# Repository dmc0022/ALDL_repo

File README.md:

# ALDL FPGA Modules

This repository contains FPGA-based hardware modules developed for the
Advanced Logic Design Lab (ALDL) project.

## Modules
- Accel-Demo: Accelerometer modules and demo
- CAP1188: Capacitive touch sensor demos
- HUB75: RGB LED matrix driver and animations
- LCD_Display: ILI9341 LCD + Breakout game renderer + keypad touch event handler/renderer 
- Schematics: Hardware schematics and PCB files
- Sensor Board: Comprehensive top file for both the LCD and CAP1188 board. Includes interfacing with the breakout connectors with a TMP117 temperature sensor via I2C.
- 3D-Models: Models of standoffs for LCD display as well as other STL files and UAH logo

Each module is self-contained and includes its own Quartus project files.

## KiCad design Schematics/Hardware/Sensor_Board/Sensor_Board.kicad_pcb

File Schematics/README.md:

# ALDL_Repo
collection of schematics, VHDL, CAD files for CPE 495 Project

3D Render of Sensor Board:

3D Render of LED Driver Board:

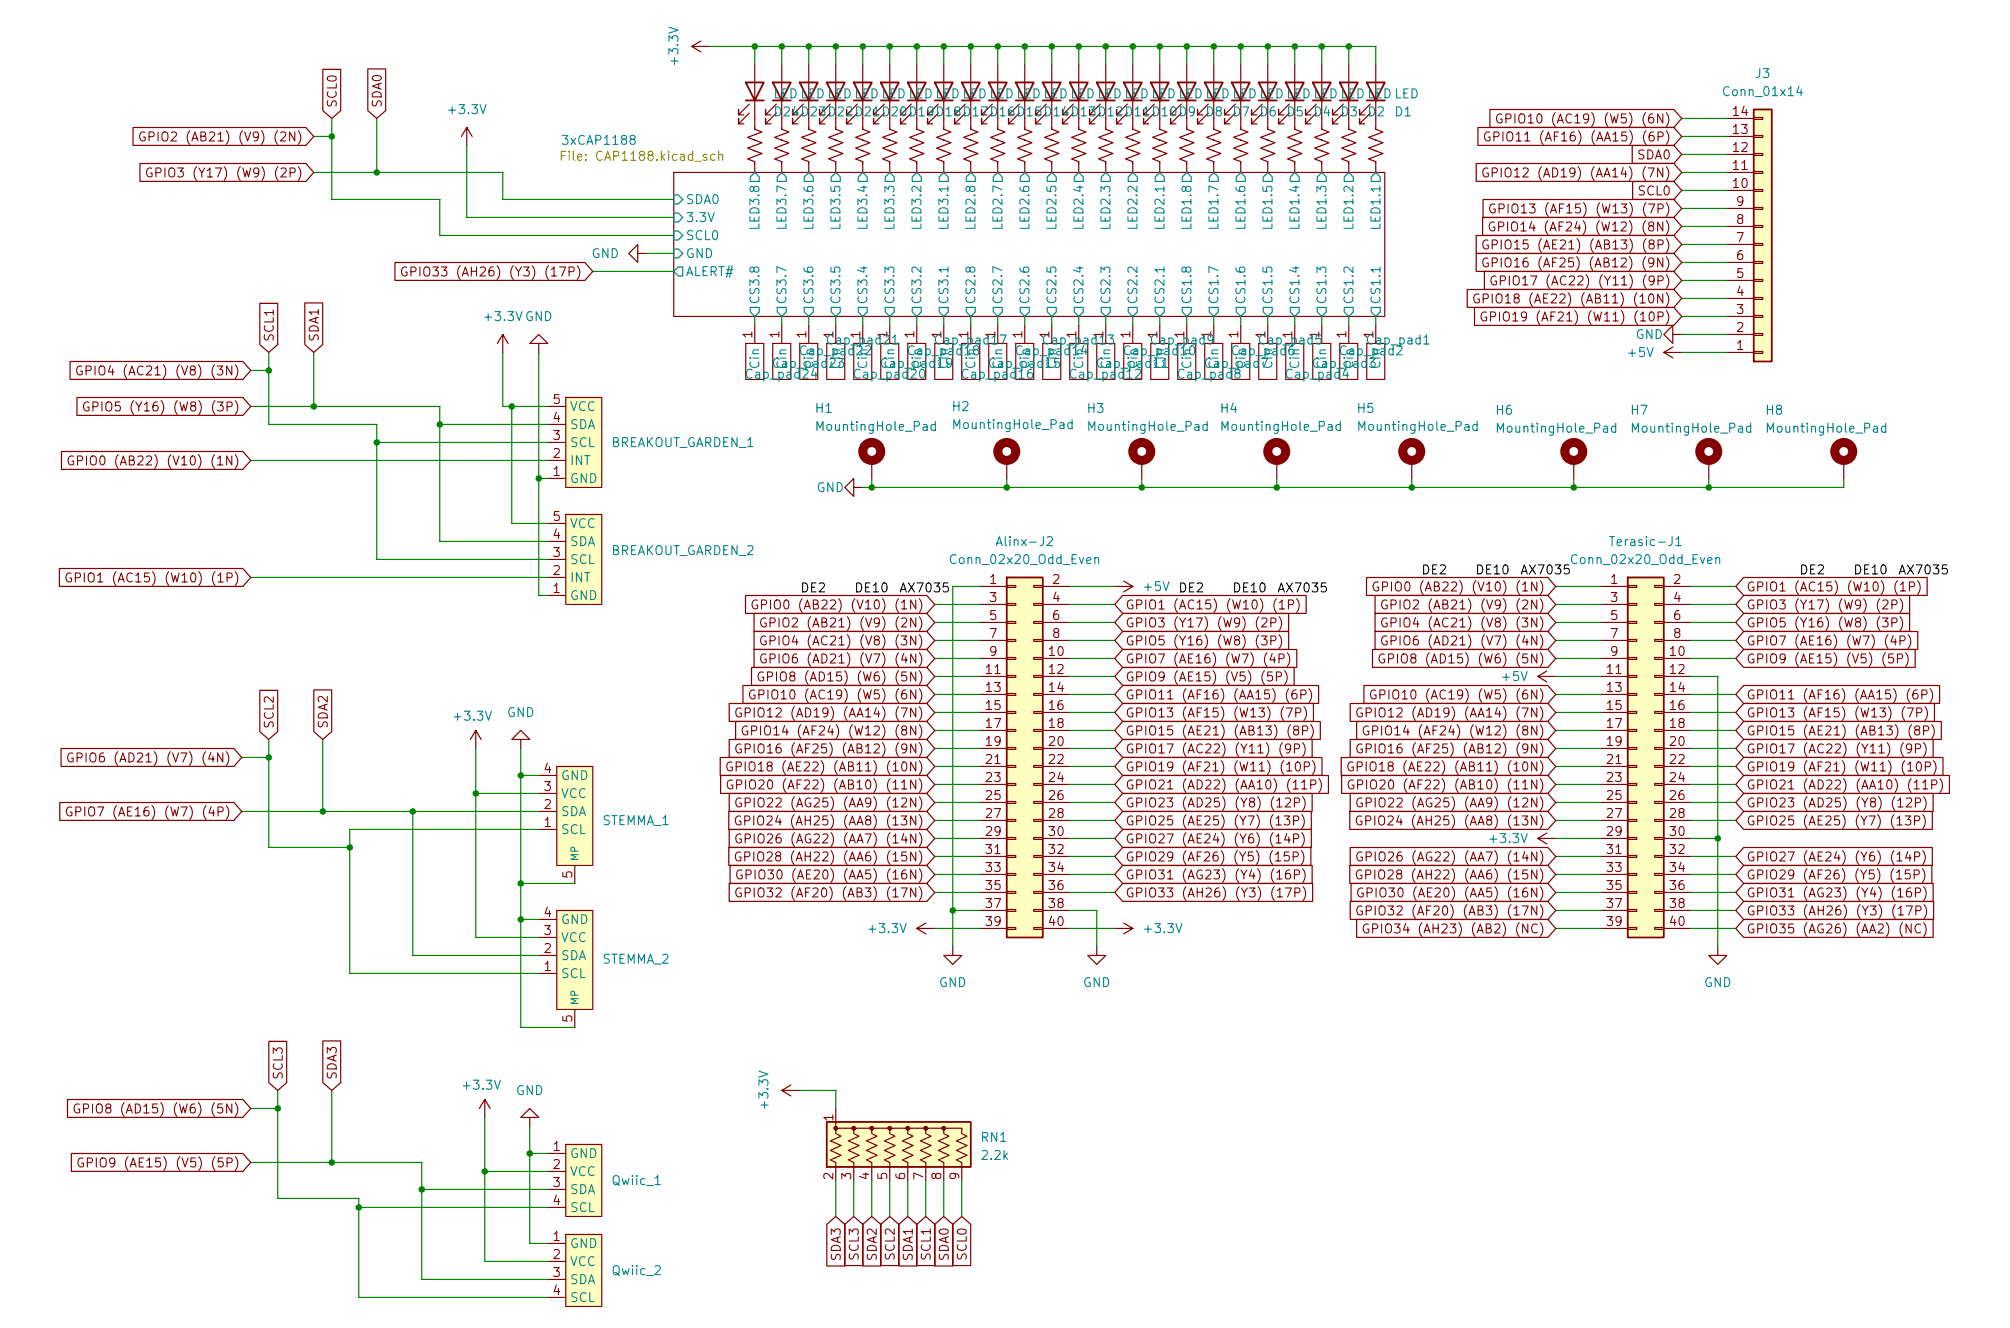
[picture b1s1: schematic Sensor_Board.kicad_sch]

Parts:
Alinx-J2: Conn_02x20_Odd_Even; IDC-Header_2x20_P2.54mm_Vertical
BREAKOUT_GARDEN_1, BREAKOUT_GARDEN_2: PinHeader_1x05_P2.54mm_Vertical
Cap_pad1, Cap_pad2, Cap_pad3, Cap_pad4, Cap_pad5, Cap_pad6, Cap_pad7, Cap_pad8, Cap_pad9, Cap_pad10, Cap_pad11, Cap_pad12, Cap_pad13, Cap_pad14, Cap_pad15, Cap_pad16, Cap_pad17, Cap_pad18, Cap_pad19, Cap_pad20, Cap_pad21, Cap_pad22, Cap_pad23, Cap_pad24: Cap_pad
D1, D2, D3, D4, D5, D6, D7, D8, D9, D10, D11, D12, D13, D14, D15, D16, D17, D18, D19, D20, D21, D22, D23, D24: LED; D_0805_2012Metric
H1, H2, H3, H4, H5, H6, H7, H8: MountingHole_Pad; MountingHole_2.5mm_Pad_Via
J3: Conn_01x14; PinSocket_1x14_P2.54mm_Vertical
Qwiic_1, Qwiic_2: JST_SH_SM04B-SRSS-TB_1x04-1MP_P1.00mm_Horizontal
R7, R8, R9, R10, R11, R12, R13, R14, R15, R16, R17, R18, R19, R20, R21, R22, R23, R24, R25, R26, R27, R28, R29, R30: 2.2k; R_0805_2012Metric
RN1: 2.2k; R_Array_SIP9
STEMMA_1, STEMMA_2: JST_PH_S4B-PH-SM4-TB_1x04-1MP_P2.00mm_Horizontal
Terasic-J1: Conn_02x20_Odd_Even; IDC-Header_2x20_P2.54mm_Vertical

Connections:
+3.3V: Alinx-J2.39, Alinx-J2.40, BREAKOUT_GARDEN_1.5 (VCC), BREAKOUT_GARDEN_2.5 (VCC), D1.2 (A), D2.2 (A), D3.2 (A), D4.2 (A), D5.2 (A), D6.2 (A), D7.2 (A), D8.2 (A), D9.2 (A), D10.2 (A), D11.2 (A), D12.2 (A), D13.2 (A), D14.2 (A), D15.2 (A), D16.2 (A), D17.2 (A), D18.2 (A), D19.2 (A), D20.2 (A), D21.2 (A), D22.2 (A), D23.2 (A), D24.2 (A), Qwiic_1.2 (VCC), Qwiic_2.2 (VCC), RN1.1 (common), STEMMA_1.3 (VCC), STEMMA_2.3 (VCC), Terasic-J1.29; also elsewhere on the board
+5V: Alinx-J2.2, J3.1, Terasic-J1.11
/3xCAP1188/CS1.1: Cap_pad1.1 (Cin); also elsewhere on the board
/3xCAP1188/CS1.2: Cap_pad2.1 (Cin); also elsewhere on the board
/3xCAP1188/CS1.3: Cap_pad3.1 (Cin); also elsewhere on the board
/3xCAP1188/CS1.4: Cap_pad4.1 (Cin); also elsewhere on the board
/3xCAP1188/CS1.5: Cap_pad5.1 (Cin); also elsewhere on the board
/3xCAP1188/CS1.6: Cap_pad6.1 (Cin); also elsewhere on the board
/3xCAP1188/CS1.7: Cap_pad7.1 (Cin); also elsewhere on the board
/3xCAP1188/CS1.8: Cap_pad8.1 (Cin); also elsewhere on the board
/3xCAP1188/CS2.1: Cap_pad9.1 (Cin); also elsewhere on the board
/3xCAP1188/CS2.2: Cap_pad10.1 (Cin); also elsewhere on the board
/3xCAP1188/CS2.3: Cap_pad11.1 (Cin); also elsewhere on the board
/3xCAP1188/CS2.4: Cap_pad12.1 (Cin); also elsewhere on the board
/3xCAP1188/CS2.5: Cap_pad13.1 (Cin); also elsewhere on the board
/3xCAP1188/CS2.6: Cap_pad14.1 (Cin); also elsewhere on the board
/3xCAP1188/CS2.7: Cap_pad15.1 (Cin); also elsewhere on the board
/3xCAP1188/CS2.8: Cap_pad16.1 (Cin); also elsewhere on the board
/3xCAP1188/CS3.1: Cap_pad17.1 (Cin); also elsewhere on the board
/3xCAP1188/CS3.2: Cap_pad18.1 (Cin); also elsewhere on the board
/3xCAP1188/CS3.3: Cap_pad19.1 (Cin); also elsewhere on the board
/3xCAP1188/CS3.4: Cap_pad20.1 (Cin); also elsewhere on the board
/3xCAP1188/CS3.5: Cap_pad21.1 (Cin); also elsewhere on the board
/3xCAP1188/CS3.6: Cap_pad22.1 (Cin); also elsewhere on the board
/3xCAP1188/CS3.7: Cap_pad23.1 (Cin); also elsewhere on the board
/3xCAP1188/CS3.8: Cap_pad24.1 (Cin); also elsewhere on the board
/3xCAP1188/LED1.1: R29.2; also elsewhere on the board
/3xCAP1188/LED1.2: R28.2; also elsewhere on the board
/3xCAP1188/LED1.3: R27.2; also elsewhere on the board
/3xCAP1188/LED1.4: R26.2; also elsewhere on the board
/3xCAP1188/LED1.5: R25.2; also elsewhere on the board
/3xCAP1188/LED1.6: R24.2; also elsewhere on the board
/3xCAP1188/LED1.7: R23.2; also elsewhere on the board
/3xCAP1188/LED1.8: R22.2; also elsewhere on the board
/3xCAP1188/LED2.1: R21.2; also elsewhere on the board
/3xCAP1188/LED2.2: R20.2; also elsewhere on the board
/3xCAP1188/LED2.3: R19.2; also elsewhere on the board
/3xCAP1188/LED2.4: R18.2; also elsewhere on the board
/3xCAP1188/LED2.5: R17.2; also elsewhere on the board
/3xCAP1188/LED2.6: R16.2; also elsewhere on the board
/3xCAP1188/LED2.7: R15.2; also elsewhere on the board
/3xCAP1188/LED2.8: R14.2; also elsewhere on the board
/3xCAP1188/LED3.1: R13.2; also elsewhere on the board
/3xCAP1188/LED3.2: R12.2; also elsewhere on the board
/3xCAP1188/LED3.3: R11.2; also elsewhere on the board
/3xCAP1188/LED3.4: R10.2; also elsewhere on the board
/3xCAP1188/LED3.5: R9.2; also elsewhere on the board
/3xCAP1188/LED3.6: R8.2; also elsewhere on the board
/3xCAP1188/LED3.7: R7.2; also elsewhere on the board
/3xCAP1188/LED3.8: R30.2; also elsewhere on the board
GND: Alinx-J2.1, Alinx-J2.37, Alinx-J2.38, BREAKOUT_GARDEN_1.1 (GND), BREAKOUT_GARDEN_2.1 (GND), H1.1, H2.1, H3.1, H4.1, H5.1, H6.1, H7.1, H8.1, J3.2, Qwiic_1.1 (GND), Qwiic_2.1 (GND), STEMMA_1.4 (GND), STEMMA_1.5 (MP), STEMMA_2.4 (GND), STEMMA_2.5 (MP), Terasic-J1.12, Terasic-J1.30; also elsewhere on the board
GPIO0 (AB22) (V10) (1N): Alinx-J2.3, BREAKOUT_GARDEN_1.2 (INT), Terasic-J1.1
GPIO1 (AC15) (W10) (1P): Alinx-J2.4, BREAKOUT_GARDEN_2.2 (INT), Terasic-J1.2
GPIO2 (AB21) (V9) (2N): Alinx-J2.5, J3.10, RN1.9 (R8), Terasic-J1.3; also elsewhere on the board
GPIO3 (Y17) (W9) (2P): Alinx-J2.6, J3.12, RN1.8 (R7), Terasic-J1.4; also elsewhere on the board
GPIO4 (AC21) (V8) (3N): Alinx-J2.7, BREAKOUT_GARDEN_1.3 (SCL), BREAKOUT_GARDEN_2.3 (SCL), RN1.7 (R6), Terasic-J1.5
GPIO5 (Y16) (W8) (3P): Alinx-J2.8, BREAKOUT_GARDEN_1.4 (SDA), BREAKOUT_GARDEN_2.4 (SDA), RN1.6 (R5), Terasic-J1.6
GPIO6 (AD21) (V7) (4N): Alinx-J2.9, RN1.5 (R4), STEMMA_1.1 (SCL), STEMMA_2.1 (SCL), Terasic-J1.7
GPIO7 (AE16) (W7) (4P): Alinx-J2.10, RN1.4 (R3), STEMMA_1.2 (SDA), STEMMA_2.2 (SDA), Terasic-J1.8
GPIO8 (AD15) (W6) (5N): Alinx-J2.11, Qwiic_1.4 (SCL), Qwiic_2.4 (SCL), RN1.3 (R2), Terasic-J1.9
GPIO9 (AE15) (V5) (5P): Alinx-J2.12, Qwiic_1.3 (SDA), Qwiic_2.3 (SDA), RN1.2 (R1), Terasic-J1.10
GPIO10 (AC19) (W5) (6N): Alinx-J2.13, J3.14, Terasic-J1.13
GPIO11 (AF16) (AA15) (6P): Alinx-J2.14, J3.13, Terasic-J1.14
GPIO12 (AD19) (AA14) (7N): Alinx-J2.15, J3.11, Terasic-J1.15
GPIO13 (AF15) (W13) (7P): Alinx-J2.16, J3.9, Terasic-J1.16
GPIO14 (AF24) (W12) (8N): Alinx-J2.17, J3.8, Terasic-J1.17
GPIO15 (AE21) (AB13) (8P): Alinx-J2.18, J3.7, Terasic-J1.18
GPIO16 (AF25) (AB12) (9N): Alinx-J2.19, J3.6, Terasic-J1.19
GPIO17 (AC22) (Y11) (9P): Alinx-J2.20, J3.5, Terasic-J1.20
GPIO18 (AE22) (AB11) (10N): Alinx-J2.21, J3.4, Terasic-J1.21
GPIO19 (AF21) (W11) (10P): Alinx-J2.22, J3.3, Terasic-J1.22
GPIO20 (AF22) (AB10) (11N): Alinx-J2.23, Terasic-J1.23
GPIO21 (AD22) (AA10) (11P): Alinx-J2.24, Terasic-J1.24
GPIO22 (AG25) (AA9) (12N): Alinx-J2.25, Terasic-J1.25
GPIO23 (AD25) (Y8) (12P): Alinx-J2.26, Terasic-J1.26
GPIO24 (AH25) (AA8) (13N): Alinx-J2.27, Terasic-J1.27
GPIO25 (AE25) (Y7) (13P): Alinx-J2.28, Terasic-J1.28
GPIO26 (AG22) (AA7) (14N): Alinx-J2.29, Terasic-J1.31
GPIO27 (AE24) (Y6) (14P): Alinx-J2.30, Terasic-J1.32
GPIO28 (AH22) (AA6) (15N): Alinx-J2.31, Terasic-J1.33
GPIO29 (AF26) (Y5) (15P): Alinx-J2.32, Terasic-J1.34
GPIO30 (AE20) (AA5) (16N): Alinx-J2.33, Terasic-J1.35
GPIO31 (AG23) (Y4) (16P): Alinx-J2.34, Terasic-J1.36
GPIO32 (AF20) (AB3) (17N): Alinx-J2.35, Terasic-J1.37
GPIO33 (AH26) (Y3) (17P): Alinx-J2.36, Terasic-J1.38; also elsewhere on the board
GPIO34 (AH23) (AB2) (NC): Terasic-J1.39
GPIO35 (AG26) (AA2) (NC): Terasic-J1.40
unnamed: D1.1 (K), R29.1
unnamed: D2.1 (K), R28.1
unnamed: D3.1 (K), R27.1
unnamed: D4.1 (K), R26.1
unnamed: D5.1 (K), R25.1
unnamed: D6.1 (K), R24.1
unnamed: D7.1 (K), R23.1
unnamed: D8.1 (K), R22.1
unnamed: D9.1 (K), R21.1
unnamed: D10.1 (K), R20.1
unnamed: D11.1 (K), R19.1
unnamed: D12.1 (K), R18.1
unnamed: D13.1 (K), R17.1
unnamed: D14.1 (K), R16.1
unnamed: D15.1 (K), R15.1
unnamed: D16.1 (K), R14.1
unnamed: D17.1 (K), R13.1
unnamed: D18.1 (K), R12.1
unnamed: D19.1 (K), R11.1
unnamed: D20.1 (K), R10.1
unnamed: D21.1 (K), R9.1
unnamed: D22.1 (K), R8.1
unnamed: D23.1 (K), R7.1
unnamed: D24.1 (K), R30.1

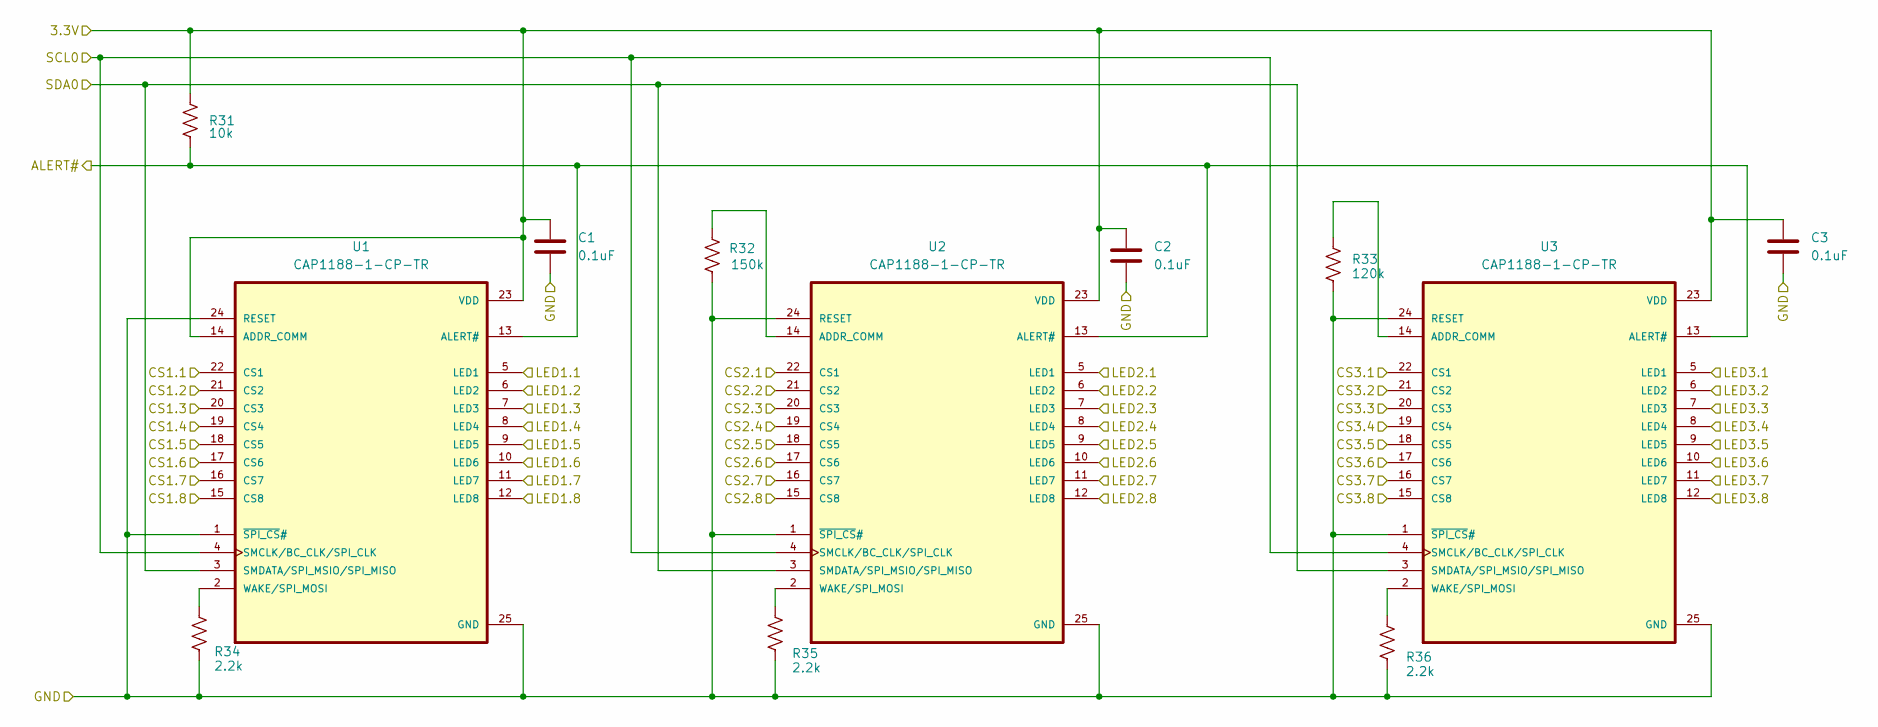
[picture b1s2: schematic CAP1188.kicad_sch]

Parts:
C1, C2, C3: 0.1uF; C_0805_2012Metric
R31: 10k; R_Axial_DIN0207_L6.3mm_D2.5mm_P10.16mm_Horizontal
R32: 150k; R_Axial_DIN0207_L6.3mm_D2.5mm_P10.16mm_Horizontal
R33: 120k; R_Axial_DIN0207_L6.3mm_D2.5mm_P10.16mm_Horizontal
R34, R35, R36: 2.2k; R_Axial_DIN0207_L6.3mm_D2.5mm_P10.16mm_Horizontal
U1, U2, U3: CAP1188-1-CP-TR; QFN-24-1EP_4x4mm_P0.5mm_EP2.7x2.6mm; PARTREV 02-09-15

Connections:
+3.3V: C1.1, C2.1, C3.1, R31.1, U1.14 (ADDR_COMM), U1.23 (VDD), U2.23 (VDD), U3.23 (VDD); also elsewhere on the board
/3xCAP1188/CS1.1: U1.22 (CS1); also elsewhere on the board
/3xCAP1188/CS1.2: U1.21 (CS2); also elsewhere on the board
/3xCAP1188/CS1.3: U1.20 (CS3); also elsewhere on the board
/3xCAP1188/CS1.4: U1.19 (CS4); also elsewhere on the board
/3xCAP1188/CS1.5: U1.18 (CS5); also elsewhere on the board
/3xCAP1188/CS1.6: U1.17 (CS6); also elsewhere on the board
/3xCAP1188/CS1.7: U1.16 (CS7); also elsewhere on the board
/3xCAP1188/CS1.8: U1.15 (CS8); also elsewhere on the board
/3xCAP1188/CS2.1: U2.22 (CS1); also elsewhere on the board
/3xCAP1188/CS2.2: U2.21 (CS2); also elsewhere on the board
/3xCAP1188/CS2.3: U2.20 (CS3); also elsewhere on the board
/3xCAP1188/CS2.4: U2.19 (CS4); also elsewhere on the board
/3xCAP1188/CS2.5: U2.18 (CS5); also elsewhere on the board
/3xCAP1188/CS2.6: U2.17 (CS6); also elsewhere on the board
/3xCAP1188/CS2.7: U2.16 (CS7); also elsewhere on the board
/3xCAP1188/CS2.8: U2.15 (CS8); also elsewhere on the board
/3xCAP1188/CS3.1: U3.22 (CS1); also elsewhere on the board
/3xCAP1188/CS3.2: U3.21 (CS2); also elsewhere on the board
/3xCAP1188/CS3.3: U3.20 (CS3); also elsewhere on the board
/3xCAP1188/CS3.4: U3.19 (CS4); also elsewhere on the board
/3xCAP1188/CS3.5: U3.18 (CS5); also elsewhere on the board
/3xCAP1188/CS3.6: U3.17 (CS6); also elsewhere on the board
/3xCAP1188/CS3.7: U3.16 (CS7); also elsewhere on the board
/3xCAP1188/CS3.8: U3.15 (CS8); also elsewhere on the board
/3xCAP1188/LED1.1: U1.5 (LED1); also elsewhere on the board
/3xCAP1188/LED1.2: U1.6 (LED2); also elsewhere on the board
/3xCAP1188/LED1.3: U1.7 (LED3); also elsewhere on the board
/3xCAP1188/LED1.4: U1.8 (LED4); also elsewhere on the board
/3xCAP1188/LED1.5: U1.9 (LED5); also elsewhere on the board
/3xCAP1188/LED1.6: U1.10 (LED6); also elsewhere on the board
/3xCAP1188/LED1.7: U1.11 (LED7); also elsewhere on the board
/3xCAP1188/LED1.8: U1.12 (LED8); also elsewhere on the board
/3xCAP1188/LED2.1: U2.5 (LED1); also elsewhere on the board
/3xCAP1188/LED2.2: U2.6 (LED2); also elsewhere on the board
/3xCAP1188/LED2.3: U2.7 (LED3); also elsewhere on the board
/3xCAP1188/LED2.4: U2.8 (LED4); also elsewhere on the board
/3xCAP1188/LED2.5: U2.9 (LED5); also elsewhere on the board
/3xCAP1188/LED2.6: U2.10 (LED6); also elsewhere on the board
/3xCAP1188/LED2.7: U2.11 (LED7); also elsewhere on the board
/3xCAP1188/LED2.8: U2.12 (LED8); also elsewhere on the board
/3xCAP1188/LED3.1: U3.5 (LED1); also elsewhere on the board
/3xCAP1188/LED3.2: U3.6 (LED2); also elsewhere on the board
/3xCAP1188/LED3.3: U3.7 (LED3); also elsewhere on the board
/3xCAP1188/LED3.4: U3.8 (LED4); also elsewhere on the board
/3xCAP1188/LED3.5: U3.9 (LED5); also elsewhere on the board
/3xCAP1188/LED3.6: U3.10 (LED6); also elsewhere on the board
/3xCAP1188/LED3.7: U3.11 (LED7); also elsewhere on the board
/3xCAP1188/LED3.8: U3.12 (LED8); also elsewhere on the board
GND: C1.2, C2.2, C3.2, R32.2, R33.2, R34.2, R35.2, R36.2, U1.1 (~SPI_CS#), U1.24 (RESET), U1.25 (GND), U2.1 (~SPI_CS#), U2.24 (RESET), U2.25 (GND), U3.1 (~SPI_CS#), U3.24 (RESET), U3.25 (GND); also elsewhere on the board
GPIO2 (AB21) (V9) (2N): U1.4 (SMCLK/BC_CLK/SPI_CLK), U2.4 (SMCLK/BC_CLK/SPI_CLK), U3.4 (SMCLK/BC_CLK/SPI_CLK); also elsewhere on the board
GPIO3 (Y17) (W9) (2P): U1.3 (SMDATA/SPI_MSIO/SPI_MISO), U2.3 (SMDATA/SPI_MSIO/SPI_MISO), U3.3 (SMDATA/SPI_MSIO/SPI_MISO); also elsewhere on the board
GPIO33 (AH26) (Y3) (17P): R31.2, U1.13 (ALERT#), U2.13 (ALERT#), U3.13 (ALERT#); also elsewhere on the board
unnamed: R34.1, U1.2 (WAKE/SPI_MOSI)
unnamed: R32.1, U2.14 (ADDR_COMM)
unnamed: R35.1, U2.2 (WAKE/SPI_MOSI)
unnamed: R33.1, U3.14 (ADDR_COMM)
unnamed: R36.1, U3.2 (WAKE/SPI_MOSI)

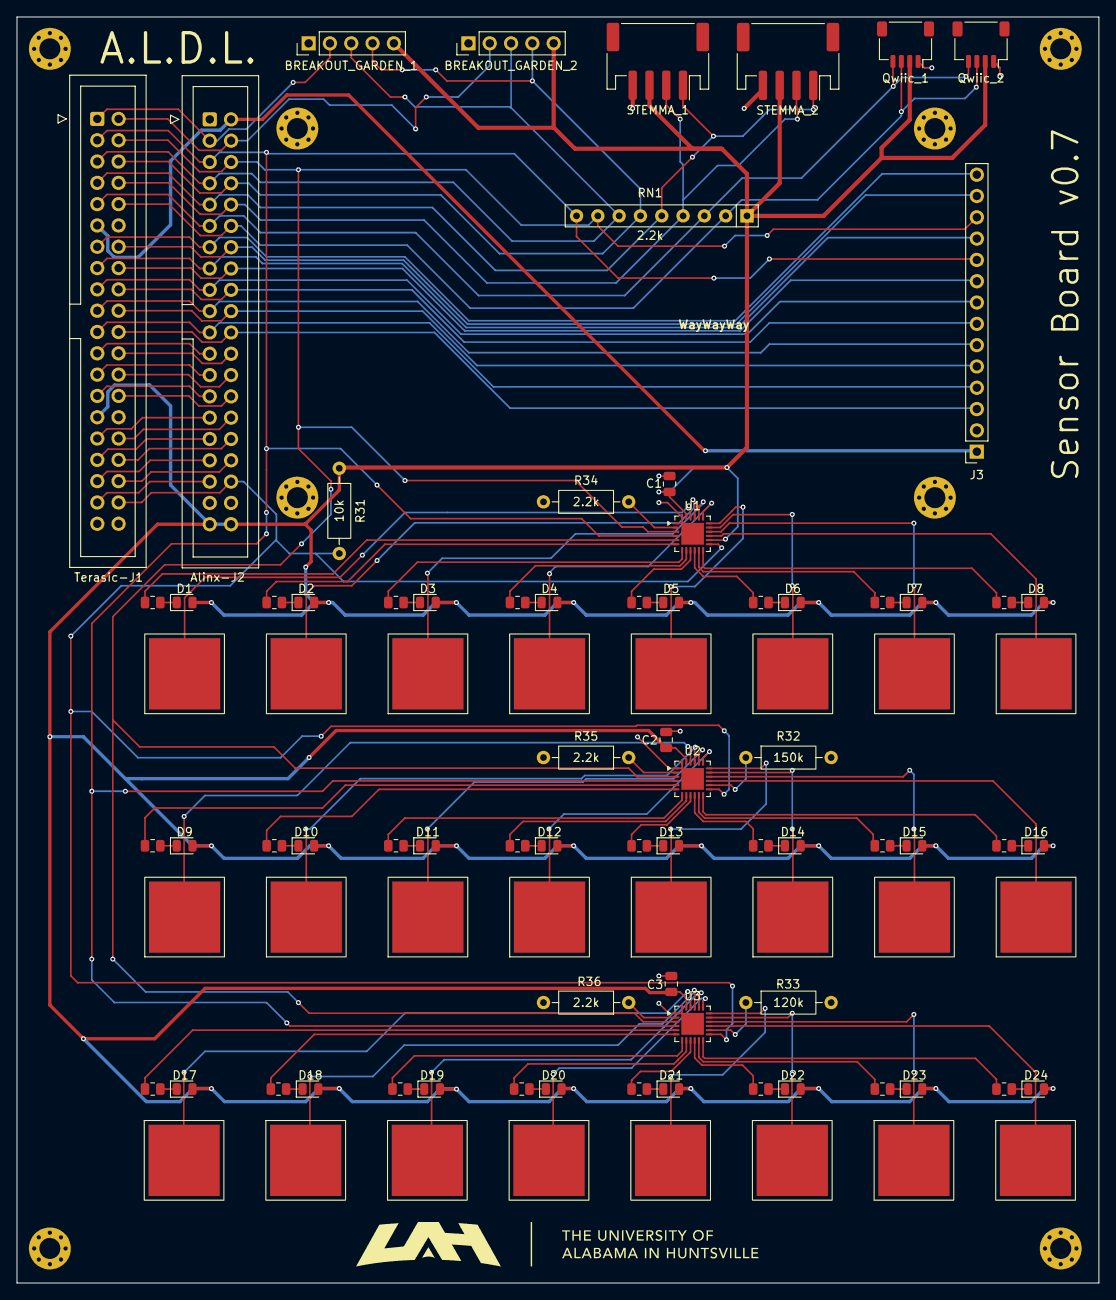
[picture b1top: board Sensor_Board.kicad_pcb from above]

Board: 2 copper layers, 129.0 x 150.9 mm, 102 parts (0 on the bottom side), 114 nets.

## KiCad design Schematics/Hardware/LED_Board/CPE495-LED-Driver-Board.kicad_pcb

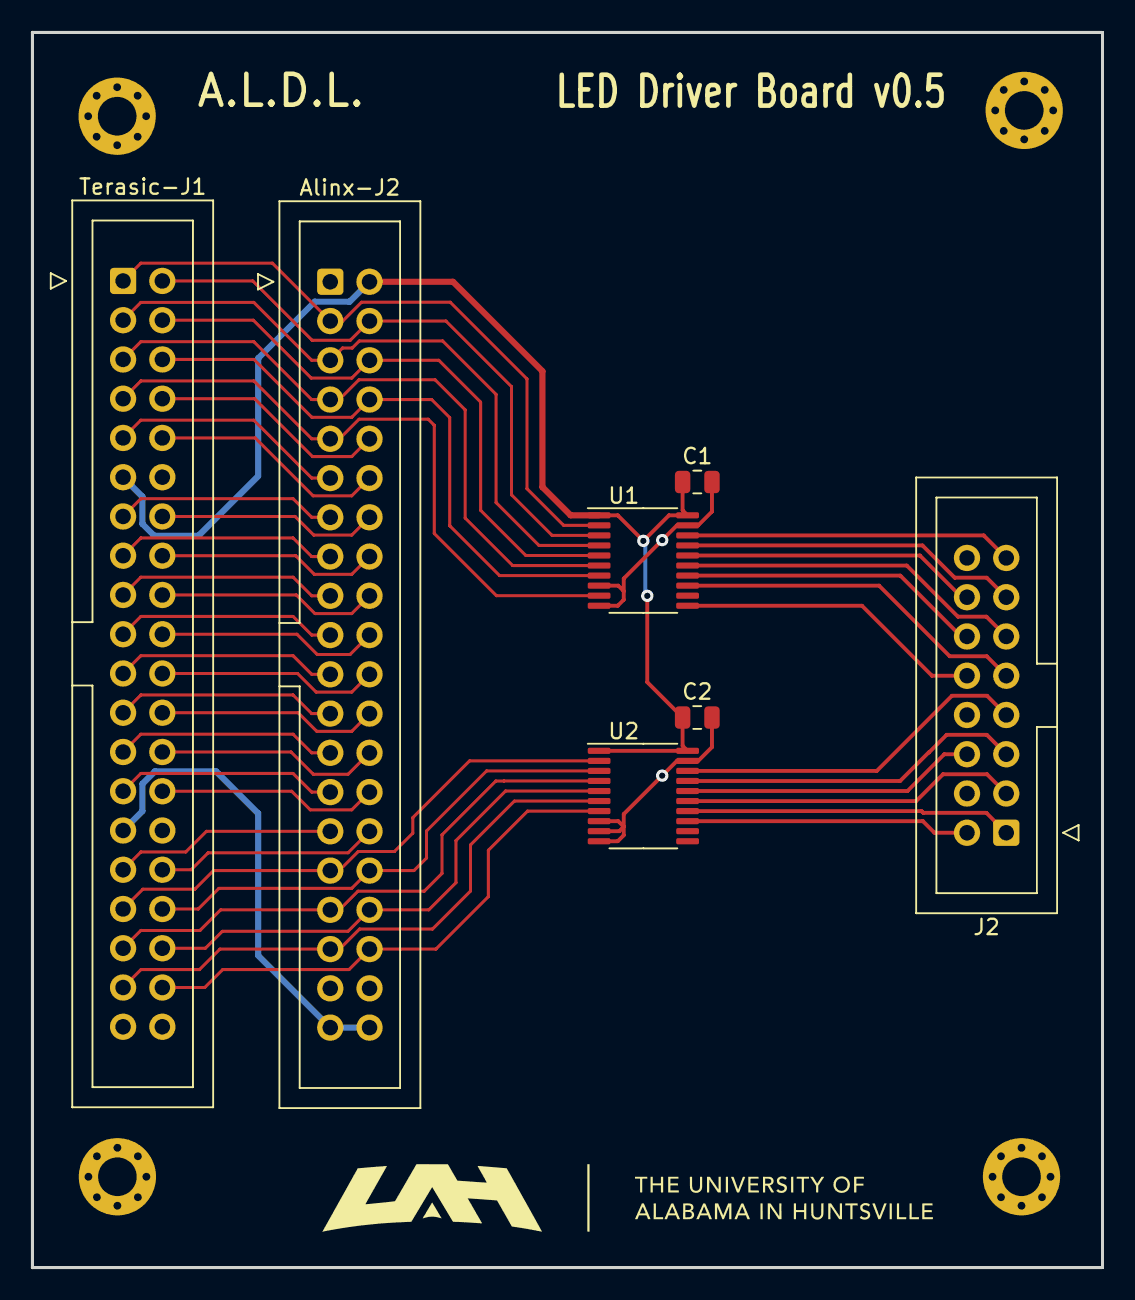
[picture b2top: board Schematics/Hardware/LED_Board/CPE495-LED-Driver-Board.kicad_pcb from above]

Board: 2 copper layers, 69.2 x 79.9 mm, 11 parts (0 on the bottom side), 50 nets.

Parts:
Alinx-J2: Conn_02x20_Odd_Even; IDC-Header_2x20_P2.54mm_Vertical
C1, C2: 0.1uF; C_0805_2012Metric
H1, H2, H3, H4: MountingHole_Pad; MountingHole_2.5mm_Pad_Via
J2: Conn_02x08_Odd_Even; IDC-Header_2x08_P2.54mm_Vertical
Terasic-J1: Conn_02x20_Odd_Even; IDC-Header_2x20_P2.54mm_Vertical
U1, U2: 74AHCT245; TSSOP-20_4.4x6.5mm_P0.65mm

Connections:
+3.3V: Alinx-J2.39, Alinx-J2.40, Terasic-J1.29
+5V: Alinx-J2.2, C1.1, C2.1, Terasic-J1.11, U1.1 (A->B), U1.20 (VCC), U2.1 (A->B), U2.20 (VCC)
A: J2.9, U1.13 (B5)
B: J2.10, U1.11 (B7)
B1: J2.3, U2.15 (B3)
B2: J2.7, U2.18 (B0)
C: J2.11, U1.15 (B3)
CLK: J2.13, U1.17 (B1)
D: J2.12, U1.14 (B4)
G1: J2.2, U2.13 (B5)
G2: J2.6, U2.16 (B2)
GND: Alinx-J2.1, Alinx-J2.37, Alinx-J2.38, C1.2, C2.2, H1.1, H2.1, H3.1, H4.1, J2.4, J2.8, J2.16, Terasic-J1.12, Terasic-J1.30, U1.8 (A6), U1.10 (GND), U1.19 (CE), U2.8 (A6), U2.9 (A7), U2.10 (GND), U2.19 (CE)
GPIO0 (AB22) (V10) (1N): Alinx-J2.3, Terasic-J1.1, U1.2 (A0)
GPIO1 (AC15) (W10) (1P): Alinx-J2.4, Terasic-J1.2, U1.3 (A1)
GPIO2 (AB21) (V9) (2N): Alinx-J2.5, Terasic-J1.3, U1.4 (A2)
GPIO3 (Y17) (W9) (2P): Alinx-J2.6, Terasic-J1.4, U1.5 (A3)
GPIO4 (AC21) (V8) (3N): Alinx-J2.7, Terasic-J1.5, U1.6 (A4)
GPIO5 (Y16) (W8) (3P): Alinx-J2.8, Terasic-J1.6, U1.7 (A5)
GPIO6 (AD21) (V7) (4N): Alinx-J2.9, Terasic-J1.7, U1.9 (A7)
GPIO7 (AE16) (W7) (4P): Alinx-J2.10, Terasic-J1.8
GPIO8 (AD15) (W6) (5N): Alinx-J2.11, Terasic-J1.9
GPIO9 (AE15) (V5) (5P): Alinx-J2.12, Terasic-J1.10
GPIO10 (AC19) (W5) (6N): Alinx-J2.13, Terasic-J1.13
GPIO11 (AF16) (AA15) (6P): Alinx-J2.14, Terasic-J1.14
GPIO12 (AD19) (AA14) (7N): Alinx-J2.15, Terasic-J1.15
GPIO13 (AF15) (W13) (7P): Alinx-J2.16, Terasic-J1.16
GPIO14 (AF24) (W12) (8N): Alinx-J2.17, Terasic-J1.17
GPIO15 (AE21) (AB13) (8P): Alinx-J2.18, Terasic-J1.18
GPIO16 (AF25) (AB12) (9N): Alinx-J2.19, Terasic-J1.19
GPIO17 (AC22) (Y11) (9P): Alinx-J2.20, Terasic-J1.20
GPIO18 (AE22) (AB11) (10N): Alinx-J2.21, Terasic-J1.21
GPIO19 (AF21) (W11) (10P): Alinx-J2.22, Terasic-J1.22
GPIO20 (AF22) (AB10) (11N): Alinx-J2.23, Terasic-J1.23
GPIO21 (AD22) (AA10) (11P): Alinx-J2.24, Terasic-J1.24
GPIO22 (AG25) (AA9) (12N): Alinx-J2.25, Terasic-J1.25
GPIO23 (AD25) (Y8) (12P): Alinx-J2.26, Terasic-J1.26
GPIO24 (AH25) (AA8) (13N): Alinx-J2.27, Terasic-J1.27
GPIO25 (AE25) (Y7) (13P): Alinx-J2.28, Terasic-J1.28
GPIO26 (AG22) (AA7) (14N): Alinx-J2.29, Terasic-J1.31
GPIO27 (AE24) (Y6) (14P): Alinx-J2.30, Terasic-J1.32
GPIO28 (AH22) (AA6) (15N): Alinx-J2.31, Terasic-J1.33, U2.2 (A0)
GPIO29 (AF26) (Y5) (15P): Alinx-J2.32, Terasic-J1.34, U2.3 (A1)
GPIO30 (AE20) (AA5) (16N): Alinx-J2.33, Terasic-J1.35, U2.4 (A2)
GPIO31 (AG23) (Y4) (16P): Alinx-J2.34, Terasic-J1.36, U2.5 (A3)
GPIO32 (AF20) (AB3) (17N): Alinx-J2.35, Terasic-J1.37, U2.6 (A4)
GPIO33 (AH26) (Y3) (17P): Alinx-J2.36, Terasic-J1.38, U2.7 (A5)
LATCH: J2.14, U1.16 (B2)
OE: J2.15, U1.18 (B0)
R1: J2.1, U2.14 (B4)
R2: J2.5, U2.17 (B1)

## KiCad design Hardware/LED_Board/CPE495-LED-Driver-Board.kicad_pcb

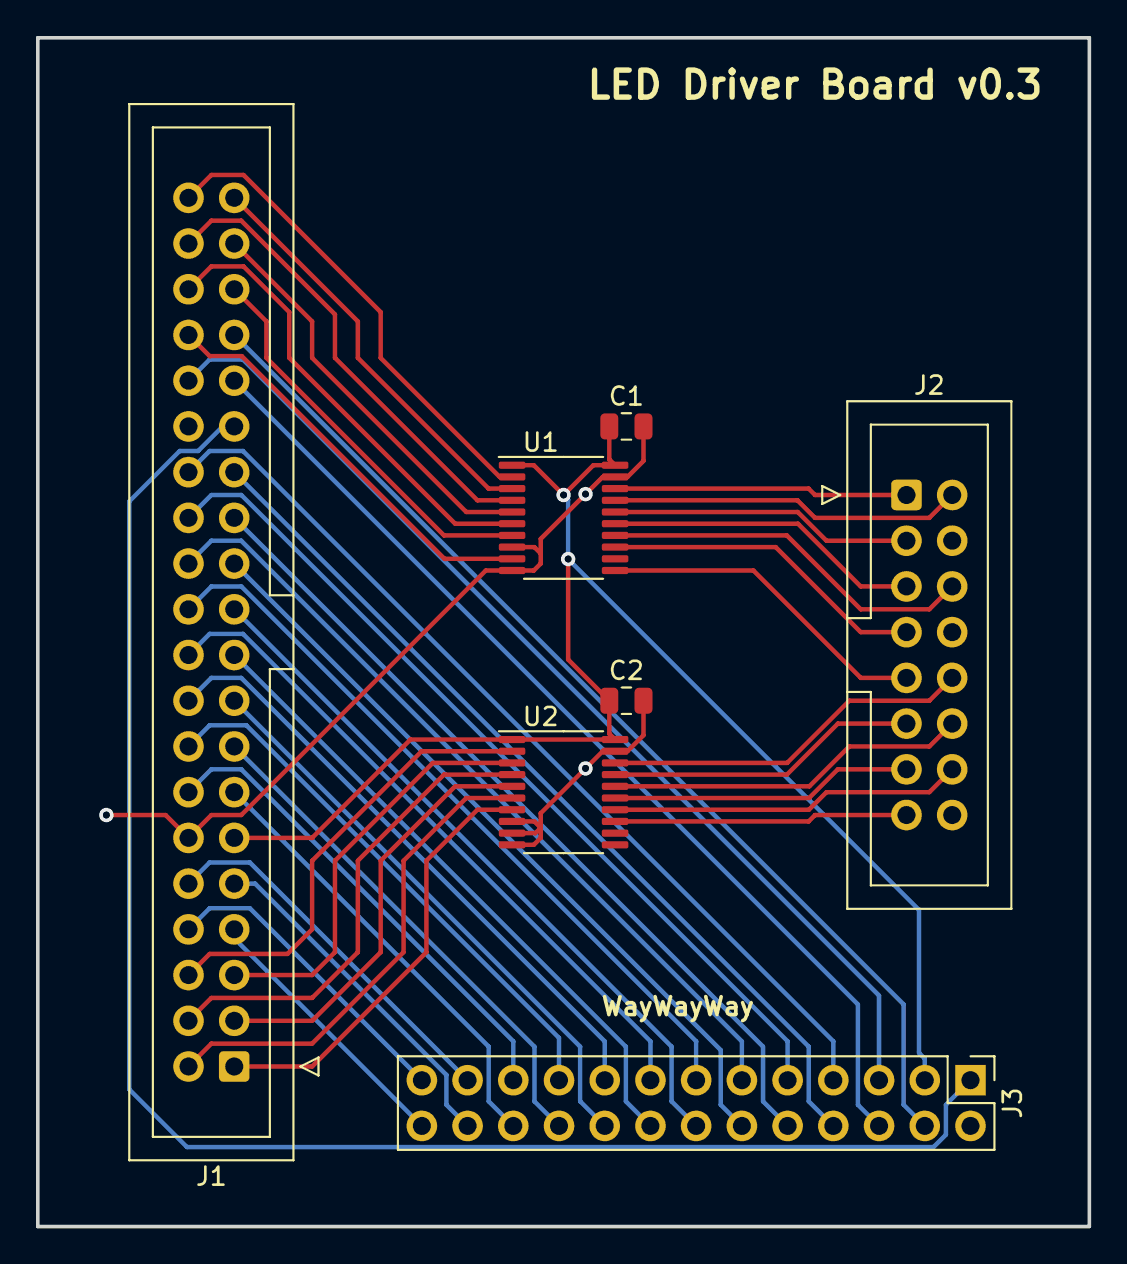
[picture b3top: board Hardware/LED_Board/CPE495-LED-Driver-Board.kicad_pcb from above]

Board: 2 copper layers, 58.4 x 66.0 mm, 7 parts (0 on the bottom side), 52 nets.

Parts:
C1, C2: 0.1uF; C_0805_2012Metric
J1: Conn_02x20_Odd_Even; IDC-Header_2x20_P2.54mm_Vertical
J2: Conn_02x08_Odd_Even; IDC-Header_2x08_P2.54mm_Vertical
J3: Conn_02x13_Odd_Even; PinHeader_2x13_P2.54mm_Vertical
U1, U2: 74AHCT245; TSSOP-20_4.4x6.5mm_P0.65mm

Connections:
+3.3V: J1.29, J3.1
+5V: C1.1, C2.1, J1.11, J3.3, U1.1 (A->B), U1.20 (VCC), U2.1 (A->B), U2.20 (VCC)
A: J2.9, U1.11 (B7)
B: J2.10, U2.18 (B0)
B1: J2.3, U1.16 (B2)
B2: J2.7, U1.13 (B5)
C: J2.11, U2.17 (B1)
CLK: J2.13, U2.15 (B3)
D: J2.12, U2.16 (B2)
G1: J2.2, U1.17 (B1)
G2: J2.6, U1.14 (B4)
GND: C1.2, C2.2, J1.12, J1.30, J2.4, J2.8, J2.16, J3.2, U1.8 (A6), U1.10 (GND), U1.19 (CE), U2.8 (A6), U2.9 (A7), U2.10 (GND), U2.19 (CE)
GPIO0 (AB22) (V10): J1.1, U2.7 (A5)
GPIO1 (AC15) (W10): J1.2, U2.6 (A4)
GPIO2 (AB21) (V9): J1.3, U2.5 (A3)
GPIO3 (Y17) (W9): J1.4, U2.4 (A2)
GPIO4 (AC21) (V8): J1.5, U2.3 (A1)
GPIO5 (Y16) (W8): J1.6, U2.2 (A0)
GPIO6 (AD21) (V7): J1.7, J3.26
GPIO7 (AE16) (W7): J1.8, J3.25
GPIO8 (AD15) (W6): J1.9, J3.24
GPIO9 (AE15) (V5): J1.10, J3.23
GPIO10 (AC19) (W5): J1.13, J3.22
GPIO11 (AF16) (AA15): J1.14, J3.21
GPIO12 (AD19) (AA14): J1.15, J3.20
GPIO13 (AF15) (W13): J1.16, J3.19
GPIO14 (AF24) (W12): J1.17, J3.18
GPIO15 (AE21) (AB13): J1.18, J3.17
GPIO16 (AF25) (AB12): J1.19, J3.16
GPIO17 (AC22) (Y11): J1.20, J3.15
GPIO18 (AE22) (AB11): J1.21, J3.14
GPIO19 (AF21) (W11): J1.22, J3.13
GPIO20 (AF22) (AB10): J1.23, J3.12
GPIO21 (AD22) (AA10): J1.24, J3.11
GPIO22 (AG25) (AA9): J1.25, J3.10
GPIO23 (AD25) (Y8): J1.26, J3.9
GPIO24 (AH25) (AA8): J1.27, J3.8
GPIO25 (AE25) (Y7): J1.28, J3.7
GPIO26 (AG22) (AA7): J1.31, J3.6
GPIO27 (AE24) (Y6): J1.32, J3.5
GPIO28 (AH22) (AA6): J1.33, J3.4
GPIO29 (AF26) (Y5): J1.34, U1.9 (A7)
GPIO30 (AE20) (AA5): J1.35, U1.7 (A5)
GPIO31 (AG23) (Y4): J1.36, U1.6 (A4)
GPIO32 (AF20) (AB3): J1.37, U1.5 (A3)
GPIO33 (AH26) (Y3): J1.38, U1.4 (A2)
GPIO34 (AH23) (AB2): J1.39, U1.3 (A1)
GPIO35 (AG26) (AA2): J1.40, U1.2 (A0)
LATCH: J2.14, U2.14 (B4)
OE: J2.15, U2.13 (B5)
R1: J2.1, U1.18 (B0)
R2: J2.5, U1.15 (B3)

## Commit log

2025-10-16 Initial I2C driver attempt
    Worked with I2C specifications doc to attempt hardcoding Write command to write data to a specified address
2025-10-16 Complete write functionality
2025-10-22 Create temp.txt
    temp
2025-10-22 Rename README.txt to README.md
2025-10-22 Update README.md
    Arghhh
2025-10-25 Deleted Hardware Directory From Main
    Trying to keep in dev branches out of main... oops
2026-01-15 Squashed 'Accel-Demo/' content from commit 3c222be
    git-subtree-dir: Accel-Demo
    git-subtree-split: 3c222be506272a43a623569fcfe3333162882c7d
2026-01-15 Squashed 'CAP1188/' content from commit 5d6b188
    git-subtree-dir: CAP1188
    git-subtree-split: 5d6b1889469c4853d95560baeedd2bcd3c731986
2026-01-15 Squashed 'HUB75/' content from commit 83a2f20
    git-subtree-dir: HUB75
    git-subtree-split: 83a2f20c2cf57addb9756d8d8f9b2e9b62d70e18
2026-01-15 Squashed 'LCD_Display/' content from commit 7b8973b
    git-subtree-dir: LCD_Display
    git-subtree-split: 7b8973b65ff3d0fba35fac86bfc1e3c39bf74e28
2026-01-15 Squashed 'Schematics/' content from commit 26693da
    git-subtree-dir: Schematics
    git-subtree-split: 26693daf98d4d713f76a8c0d4ee88679fc2fbd86
2026-01-15 Revise README to detail each folder in Main
    Removed previous branches and allocated everything to main branch
2026-01-23 Edited comments
2026-02-12 Updated LCD modules
    Fixed RGB565 colors, updated SPI module for SD card expansion, Added Keypad "app" that displays single key presses to 7-segment display
2026-02-12 updated qpf
2026-02-16 Add image to README for module visualization
    Added an image to the README for better visualization.
2026-02-16 Enhance LCD_Display module description
    Updated description for LCD_Display module to include keypad touch event handling.
2026-02-21 Add multi-device CAP1188 touch sensor module
    ***STILL NEEDS TESTING*****
2026-03-02 Created the Lab1 Code, Included the LAteX Source
2026-03-15 Updated Sensor board schematic/PCB
    Still need to double check STEMMA connector and LCD standoff placement.
2026-03-18 Added
2026-03-18 Pre-production PCB files are almost ready
    Added LCD mounting holes and spaced capacitive touch pads out more.
    All that's left is to double check and then order PCBs.
2026-03-24 integration for sensor board
2026-03-24 Rename LCD_driver_core_shared_touch.v to sensor_board/LCD_driver_core_shared_touch.v
2026-03-24 Rename aldl_system_top.qsf to sensor_board/aldl_system_top.qsf
2026-03-24 Rename aldl_system_top.v to sensor_board/aldl_system_top.v
2026-03-24 Rename ball_yellow_reduced.hex to sensor_board/ball_yellow_reduced.hex
2026-03-24 Rename breakout_game.v to sensor_board/breakout_game.v
2026-03-24 Add breakout_icon_48x48_rgb565.hex file
2026-03-24 Rename breakout_renderer.v to sensor_board/breakout_renderer.v
2026-03-24 Rename brick_green_reduced.hex to sensor_board/brick_green_reduced.hex
2026-03-24 Rename font4x7.v to sensor_board/font4x7.v
2026-03-24 Rename gI2C_low_level_tx_rx.v to sensor_board/gI2C_low_level_tx_rx.v
2026-03-24 Rename gif_renderer.v to sensor_board/gif_renderer.v
2026-03-24 Rename hex7seg.v to sensor_board/hex7seg.v
2026-03-24 Rename home_renderer.v to sensor_board/home_renderer.v
2026-03-24 Rename i2c_touch_hub.v to sensor_board/i2c_touch_hub.v
2026-03-24 Rename image_rom.v to sensor_board/image_rom.v
2026-03-24 Rename keypad_renderer.v to sensor_board/keypad_renderer.v
2026-03-24 Rename keypad_touch_decode.v to sensor_board/keypad_touch_decode.v
2026-03-24 Rename new_CAP1188.v to sensor_board/new_CAP1188.v
2026-03-24 Rename paddle_yellow_reduced.hex to sensor_board/paddle_yellow_reduced.hex
2026-03-24 Rename spi_master_byte.v to sensor_board/spi_master_byte.v
2026-03-24 Rename temperature_renderer.v to sensor_board/temperature_renderer.v
2026-03-24 Rename tft_ili9341.v to sensor_board/tft_ili9341.v
2026-03-24 Rename tft_ili9341_spi.v to sensor_board/tft_ili9341_spi.v
2026-03-24 Rename tft_ili9341_spi_wrapper.v to sensor_board/tft_ili9341_spi_wrapper.v
2026-03-24 Rename tmp117_reader.v to sensor_board/tmp117_reader.v
2026-03-25 Rename aldl_system_top.qpf to sensor_board/aldl_system_top.qpf
2026-04-08 updated integration of temperature sensor
2026-04-08 Rename i2c_master.sv to sensor_board/i2c_master.sv
2026-04-08 Rename cycle_timer.sv to sensor_board/cycle_timer.sv
2026-04-12 Final Final v0.5 sensor board PCB layout
    Fixed incorrect Qwiic and Stemma pinouts.
2026-04-16 Added support for DE10 for 32x32 matrix lab
2026-04-17 Refactor tft_ili9341_spi module for clarity
2026-04-17 Refine comment in I2C master design
    Updated comment to remove 'Debug-patched' from the description.
2026-04-17 Refactor breakout game logic for consistent updates
    Refactor breakout game logic to ensure consistent game state updates on a fixed-rate tick derived from clk, improving smoothness regardless of display SPI speed. Update comments to reflect changes in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
2026-04-17 Refactor hex7seg module comments and formatting
2026-04-17 Refactor keypad_renderer.v for improved clarity
2026-04-17 Update panel-specific notes for color correction
2026-04-17 Refine comments in TFT SPI Wrapper
    Updated comments for clarity and consistency.
2026-04-17 Remove redundant comment from sensor board file
2026-04-17 Add debug output comments to I2C master
    Added comments for debug outputs including FSM state and counters.
2026-04-17 Document TMP117 sensor details in tmp117_reader.v
    Added comments explaining TMP117 sensor functionality and temperature range.
2026-04-17 Add debug outputs to I2C master module
    Added debug outputs for FSM state and counters.
2026-04-25 Removed old gerbers and drill files
2026-04-25 v0.7 Sensor Board Files
    Fixed LCD footprint to now include GND.
    Fixed Qwiic connector pinout.
2026-04-25 v0.7 Sensor Board Gerbers
    Fixed LCD and Qwiic Gerbers.
2026-04-25 v0.7 Sensor Board Centroid Files for Assembly
2026-04-25 v0.7 Sensor Board Bill Of Materials
2026-04-25 v0.5 LED Driver Board Gerbers/Centroid Files
2026-04-25 Updated DE10-Lite pinouts for new Sensor Board
    Currently configured for STEMMA
2026-04-29 Added 11mm standoffs for LCD screen
2026-04-30 Update README with module descriptions
    Added descriptions for LCD_Display and Sensor Board and 3D model modules.
2026-04-30 add read me to sensor board folder
2026-04-30 added STL files and UAH logo
2026-04-30 batch conversion file for 32x32 gifs to RBG565
2026-04-30 add manuals
2026-04-30 Rename DE10-Lite_User_Manual (3).pdf to Documentation/DE10-Lite_User_Manual (3).pdf
2026-05-01 Clarify 3D-Models section in README
    Updated the 3D-Models section to specify the contents more clearly.
2026-05-01 Fix typo in 3D-Models section of README
2026-05-01 added various hex files for different GIF options
2026-05-01 added Lab2 manual/files
2026-05-01 Rename A_L_D_L__Lab_2.pdf to ALDL_LAB2/A_L_D_L__Lab_2.pdf
2026-05-01 added the rest of Lab 2 files
2026-05-01 Small update to Sensor v0.7 BOM
2026-05-01 Uploaded LED v0.5 BOM
2026-05-01 Update aldl_system_top.qsf
    current pinout for TMP SCL and SDA for TMP117
2026-05-01 Update aldl_system_top.v
    enabled 3rd cow CAP1188 and set device address for 120k resistor
2026-05-03 Add data sheets
2026-05-03 Component Documents
